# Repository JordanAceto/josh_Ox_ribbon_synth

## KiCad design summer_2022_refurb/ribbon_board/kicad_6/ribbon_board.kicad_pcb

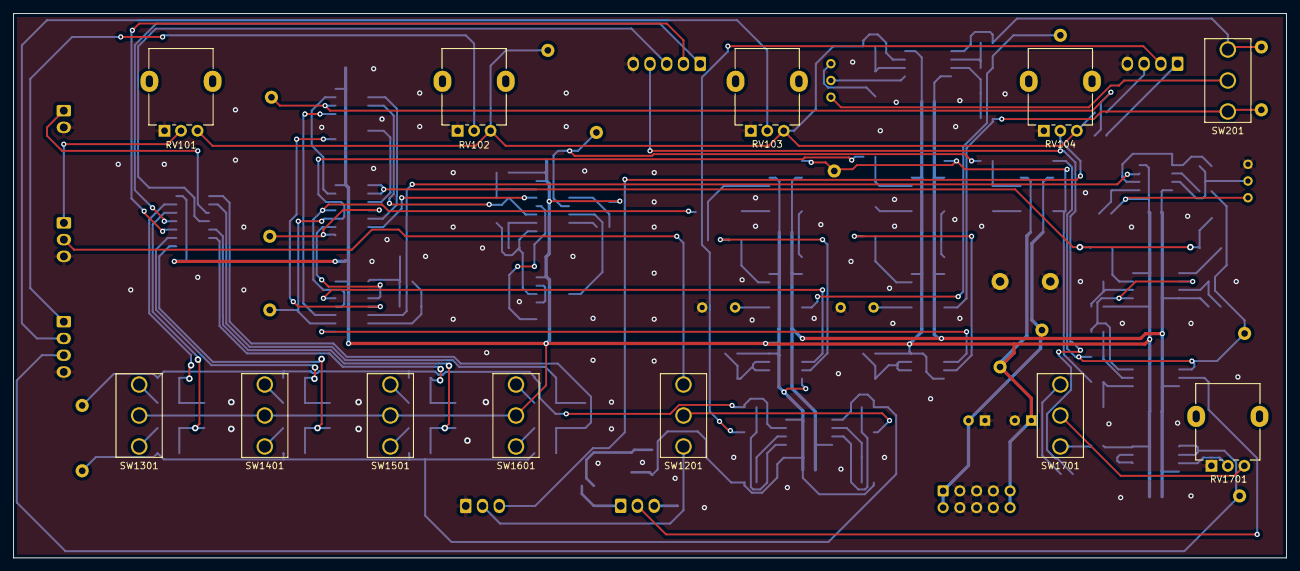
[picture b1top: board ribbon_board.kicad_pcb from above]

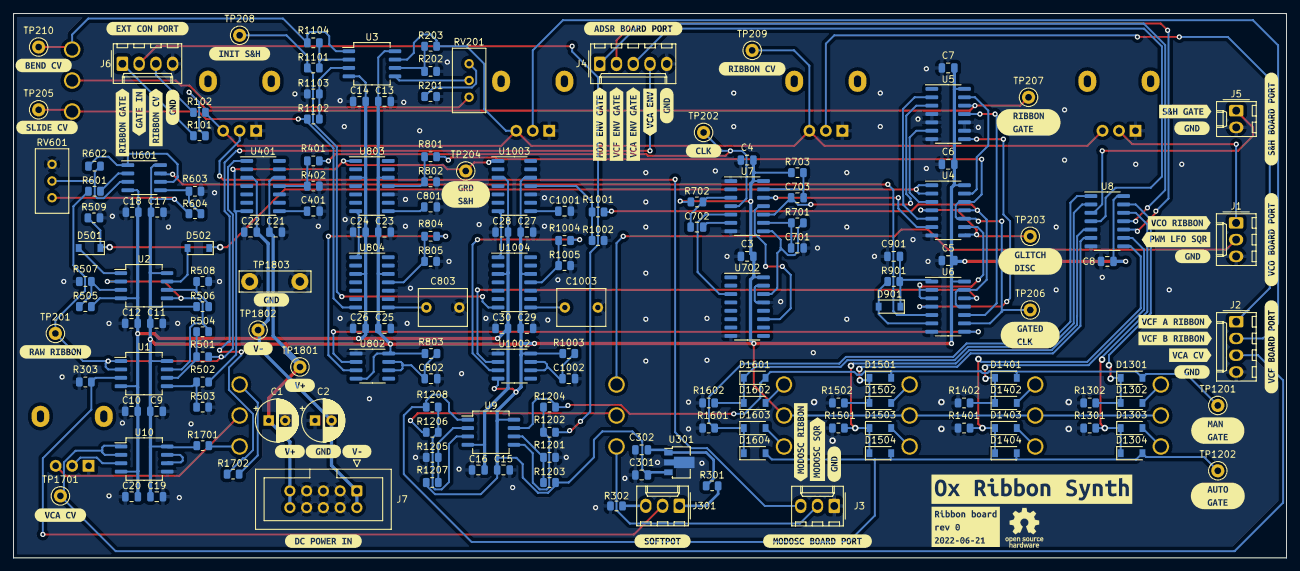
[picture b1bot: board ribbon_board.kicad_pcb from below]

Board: 2 copper layers, 193.0 x 82.5 mm, 229 parts (217 on the bottom side), 115 nets.

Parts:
C1, C2: 10u; CP_Radial_D6.3mm_P2.50mm
C3, C4, C5, C6, C7, C8, C9, C10, C11, C12, C13, C14, C15, C16, C17, C18, C19, C20, C21, C22, C23, C24, C25, C26, C27, C28, C29, C30, C302: 100n; C_0805_2012Metric
C301: 470n; C_0805_2012Metric
C401, C801, C1001: 2n2; C_0805_2012Metric
C701: 1n; C_0805_2012Metric
C702, C703: 4n7; C_0805_2012Metric
C802, C901, C1002: 10n; C_0805_2012Metric
C803, C1003: 1u; C_Rect_L7.2mm_W5.5mm_P5.00mm_FKS2_FKP2_MKS2_MKP2
D501, D502, D901, D1301, D1302, D1303, D1304, D1401, D1402, D1403, D1404, D1501, D1502, D1503, D1504, D1601, D1602, D1603, D1604: 1N4148W; D_SOD-123
J1: VCO_port; Molex_KK-254_AE-6410-03A_1x03_P2.54mm_Vertical
J2: VCF_port; Molex_KK-254_AE-6410-04A_1x04_P2.54mm_Vertical
J3: mod_osc_port; Molex_KK-254_AE-6410-03A_1x03_P2.54mm_Vertical
J4: ADSR_port; Molex_KK-254_AE-6410-05A_1x05_P2.54mm_Vertical
J5: S&H_port; Molex_KK-254_AE-6410-02A_1x02_P2.54mm_Vertical
J6: ext_port; Molex_KK-254_AE-6410-04A_1x04_P2.54mm_Vertical
J7: power_entry; IDC-Header_2x05_P2.54mm_Vertical
J301: ribbon; Molex_KK-254_AE-6410-03A_1x03_P2.54mm_Vertical
R101, R102: 1k; R_0805_2012Metric
R201, R603, R702, R703, R1201, R1202, R1205, R1206: 10k; R_0805_2012Metric
R202, R203, R501, R502, R503, R504, R509, R601, R602, R604, R701, R1101, R1102, R1103, R1104, R1203, R1207, R1301, R1302, R1401, R1402, R1501, R1502, R1601, R1602, R1702: 100k; R_0805_2012Metric
R301: 100; R_0805_2012Metric
R302: 4k7; R_0805_2012Metric
R303, R803, R1003, R1204, R1208: 1M2; R_0805_2012Metric
R401, R801, R804, R1001, R1004: 5k6; R_0805_2012Metric
R402, R802, R805, R1002, R1005: 1k8; R_0805_2012Metric
R505, R506, R1701: 150k; R_0805_2012Metric
R507, R508: 470; R_0805_2012Metric
R901: 120k; R_0805_2012Metric
RV101, RV102, RV103, RV104: 100k c.d.; Potentiometer_Alpha_RD901F-40-00D_Single_Vertical
RV201, RV601: 100k; Potentiometer_Bourns_3296W_Vertical
RV1701: 100k; Potentiometer_Alpha_RD901F-40-00D_Single_Vertical
SW201, SW1201, SW1701: SW_SPDT; SPDT_mini_toggle
SW1301, SW1401, SW1501, SW1601: SW_SPDT_MSM; SPDT_mini_toggle
TP201: raw_ribbon; TestPoint_Keystone_5000-5004_Miniature
TP202: clk; TestPoint_Keystone_5000-5004_Miniature
TP203: glitch_dis; TestPoint_Keystone_5000-5004_Miniature
TP204: guard_s_and_h; TestPoint_Keystone_5000-5004_Miniature
TP205: slide_s_and_h; TestPoint_Keystone_5000-5004_Miniature
TP206: gated_clk; TestPoint_Keystone_5000-5004_Miniature
TP207: gate; TestPoint_Keystone_5000-5004_Miniature
TP208: init_s_and_h; TestPoint_Keystone_5000-5004_Miniature
TP209: ribbon_cv; TestPoint_Keystone_5000-5004_Miniature
TP210: bend_cv; TestPoint_Keystone_5000-5004_Miniature
TP1201: man_gate; TestPoint_Keystone_5000-5004_Miniature
TP1202: audo_gate; TestPoint_Keystone_5000-5004_Miniature
TP1701: vca_cv; TestPoint_Keystone_5000-5004_Miniature
TP1801: V+; TestPoint_Keystone_5000-5004_Miniature
TP1802: V-; TestPoint_Keystone_5000-5004_Miniature
TP1803: GND; TestPoint_Bridge_Pitch7.62mm_Drill1.3mm
U1, U2, U3, U9, U10: TL072; SO-8_5.3x6.2mm_P1.27mm
U4, U8: 4081; SOIC-14_3.9x8.7mm_P1.27mm
U5: 4013; SOIC-14_3.9x8.7mm_P1.27mm
U6, U7: 40106; SOIC-14_3.9x8.7mm_P1.27mm
U301: L78L10_SOT89; SOT-89-3
U401, U803, U804, U1003, U1004: LF398_SOIC14; SOIC-14_3.9x8.7mm_P1.27mm
U601: LM358; SOIC-8_3.9x4.9mm_P1.27mm
U702: 4017; SOIC-16_3.9x9.9mm_P1.27mm
U802, U1002: TLC555xD; SOIC-8_3.9x4.9mm_P1.27mm
kibuzzard-62AC7A9F: G***; kibuzzard-62AC7A9F
kibuzzard-62B1F2D1, kibuzzard-62B1F2D1#2, kibuzzard-62B1F2D1#3, kibuzzard-62B1F2D1#4, kibuzzard-62B1F2D1#5, kibuzzard-62B1F2D1#6, kibuzzard-62B1F2D1#7, kibuzzard-62B1F2D1#8: G***; kibuzzard-62B1F2D1
kibuzzard-62B1F3ED: G***; kibuzzard-62B1F3ED
kibuzzard-62B1F4B1: G***; kibuzzard-62B1F4B1
kibuzzard-62B1F4C1: G***; kibuzzard-62B1F4C1
kibuzzard-62B1F7DB: G***; kibuzzard-62B1F7DB
kibuzzard-62B1F7F1: G***; kibuzzard-62B1F7F1
kibuzzard-62B1F8A8: G***; kibuzzard-62B1F8A8
kibuzzard-62B1F8CB: G***; kibuzzard-62B1F8CB
kibuzzard-62B1F8F4: G***; kibuzzard-62B1F8F4
kibuzzard-62B1F9D0: G***; kibuzzard-62B1F9D0
kibuzzard-62B1F45D: G***; kibuzzard-62B1F45D
kibuzzard-62B1F49A: G***; kibuzzard-62B1F49A
kibuzzard-62B1F53B: G***; kibuzzard-62B1F53B
kibuzzard-62B1F72D: G***; kibuzzard-62B1F72D
kibuzzard-62B1F77F: G***; kibuzzard-62B1F77F
kibuzzard-62B1F525: G***; kibuzzard-62B1F525
kibuzzard-62B1F567: G***; kibuzzard-62B1F567
kibuzzard-62B1F712: G***; kibuzzard-62B1F712
kibuzzard-62B1F743: G***; kibuzzard-62B1F743
kibuzzard-62B1F752: G***; kibuzzard-62B1F752
kibuzzard-62B1F821: G***; kibuzzard-62B1F821
kibuzzard-62B1F904: G***; kibuzzard-62B1F904
kibuzzard-62B1F917: G***; kibuzzard-62B1F917
kibuzzard-62B1F959, kibuzzard-62B1F959#2: G***; kibuzzard-62B1F959
kibuzzard-62B1F963, kibuzzard-62B1F963#2: G***; kibuzzard-62B1F963
kibuzzard-62B1FC16: G***; kibuzzard-62B1FC16
kibuzzard-62B1FC43: G***; kibuzzard-62B1FC43
kibuzzard-62B1FC58: G***; kibuzzard-62B1FC58
kibuzzard-62B1FC81: G***; kibuzzard-62B1FC81
kibuzzard-62B1FCCC: G***; kibuzzard-62B1FCCC
kibuzzard-62B1FD45: G***; kibuzzard-62B1FD45
kibuzzard-62B1FD51: G***; kibuzzard-62B1FD51
kibuzzard-62B1FD62: G***; kibuzzard-62B1FD62
kibuzzard-62B1FDDB: G***; kibuzzard-62B1FDDB
kibuzzard-62B1FE6D: G***; kibuzzard-62B1FE6D
kibuzzard-62B1FEB0: G***; kibuzzard-62B1FEB0
kibuzzard-62B1FECC: G***; kibuzzard-62B1FECC
kibuzzard-62B235EB: G***; kibuzzard-62B235EB
kibuzzard-62B239A3: G***; kibuzzard-62B239A3
kibuzzard-62B23681: G***; kibuzzard-62B23681

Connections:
+15V: C1.1, C3.1, C4.1, C5.1, C6.1, C7.1, C8.1, C9.1, C11.1, C13.1, C15.1, C17.1, C19.1, C21.1, C23.1, C25.1, C27.1, C29.1, C301.1, J7.9, J7.10, R506.1, R604.2, R702.1, R703.1, R803.1, R1003.1, R1203.2, R1207.2, R1701.1, RV601.3, SW1301.2, SW1401.2, SW1501.2, SW1601.2, TP1801.1, U1.8 (V+), U2.8 (V+), U3.8 (V+), U4.14 (VDD), U5.14 (VDD), U6.14 (VDD), U7.14 (VDD), U8.14 (VDD), U9.8 (V+), U10.8 (V+), U301.3 (IN), U401.12 (V+), U601.8 (V+), U702.16 (VDD), U802.4 (R), U802.8 (VCC), U803.12 (V+), U804.12 (V+), U1002.4 (R), U1002.8 (VCC), U1003.12 (V+), U1004.12 (V+)
-15V: C2.2, C10.2, C12.2, C14.2, C16.2, C18.2, C20.2, C22.2, C24.2, C26.2, C28.2, C30.2, J7.1, J7.2, R505.2, TP1802.1, U1.4 (V-), U2.4 (V-), U3.4 (V-), U9.4 (V-), U10.4 (V-), U401.3 (V-), U601.4 (V-), U803.3 (V-), U804.3 (V-), U1003.3 (V-), U1004.3 (V-)
/GATE_IN: J6.2, R1202.1
/MOD_OSC_RIBBON_CTL: J3.3, RV104.2
/MOD_OSC_SQR: J3.2, SW1201.1 (A)
/PWM_LFO_SQR: J1.2, SW1201.3 (C)
/RIBBON_CV: R102.2, R203.2, RV101.3, RV102.3, RV103.3, RV104.3, TP209.1, U3.7
/RIBBON_GATE: R101.2, TP207.1, U5.12 (~Q)
/VCA_ADSR: J4.4, R1702.1
/VCA_CV: J2.3, TP1701.1, U10.1, U10.2 (-)
/VCF_A_RIBBON_CTL: J2.1, RV102.2
/VCF_B_RIBBON_CTL: J2.2, RV103.2
/VCO_RIBBON_CTL: J1.1, RV101.2
/gate_controller/MOD_ENV_GATE: J4.1, U8.11
/gate_controller/S&H_GATE: J5.1, U8.3
/gate_controller/VCA_ADSR_gate_logic/AUTO_GATE: D1304.2 (A), D1404.2 (A), D1504.2 (A), D1604.2 (A), R1208.2, TP1202.1, U9.1
/gate_controller/VCA_ADSR_gate_logic/RIBBON_GATE: D1301.2 (A), D1401.2 (A), D1501.2 (A), D1601.2 (A), R1204.2, TP1201.1, U9.7
/gate_controller/VCA_ENV_GATE: J4.3, U8.4
/gate_controller/VCF_ENV_GATE: J4.2, U8.10
/ribbon_controller/BEND_CV: R1104.2, SW201.3 (C), TP210.1, U3.1
/ribbon_controller/SLIDE_CV: R1102.1, SW201.1 (A), TP205.1, U804.7
/ribbon_controller/TRIG_0: R401.1, TP202.1, U7.4
/ribbon_controller/TRIG_9: U4.6, U7.12
/ribbon_controller/bend_scaler/INIT_IN: R1101.1, TP208.1, U1004.7
/ribbon_controller/comparator/COMP_OUT: U6.5, U601.7
/ribbon_controller/comparator/SIGNAL_IN: R501.1, R601.1, TP201.1, U1.1, U1.2 (-), U401.1 (I)
/ribbon_controller/gate_conditioner/GATED_CLK: R801.1, TP206.1, U4.10, U4.12, U6.9
/ribbon_controller/gate_conditioner/GD_IN: TP203.1, U4.4, U4.8
/ribbon_controller/gate_conditioner/S&H_TRIG: R1001.1, U4.11, U6.11, U6.13
/ribbon_controller/glitch_discriminator/S&H_RIBBON: R502.1, TP204.1, U401.7, U803.1 (I), U1003.1 (I)
/ribbon_controller/~CLK_9: C703.1, U5.3 (C), U7.10
GND: C1.2, C2.1, C3.2, C4.2, C5.2, C6.2, C7.2, C8.2, C9.2, C10.1, C11.2, C12.1, C13.2, C14.1, C15.2, C16.1, C17.2, C18.1, C19.2, C20.1, C21.2, C22.1, C23.2, C24.1, C25.2, C26.1, C27.2, C28.1, C29.2, C30.1, C301.2, C302.2, C401.2, C701.2, C801.2, C802.2, C803.2, C901.2, C1001.2, C1002.2, C1003.2, J1.3, J2.4, J3.1, J4.5, J5.2, J6.4, J7.3, J7.4, J7.5, J7.6, J7.7, J7.8, R201.2, R202.1, R302.2, R303.2, R402.2, R503.2, R507.1, R508.2, R509.2, R603.1, R802.2, R805.2, R1002.2, R1005.2, R1103.1, R1201.1, R1205.1, R1301.2, R1302.2, R1401.2, R1402.2, R1501.2, R1502.2, R1601.2, R1602.2, RV101.1, RV102.1, RV103.1, RV104.1, RV601.1, RV1701.1, TP1803.1, U4.7 (VSS), U5.4 (R), U5.5 (D), U5.7 (VSS), U5.9 (D), U5.10 (R), U6.7 (VSS), U7.1, U7.7 (VSS), U8.7 (VSS), U10.5 (+), U301.2 (GND), U401.10 (T), U702.8 (VSS), U702.13 (CKEN), U702.15 (Reset), U802.1 (GND), U803.10 (T), U804.10 (T), U1002.1 (GND), U1003.10 (T), U1004.10 (T)
unnamed: C302.1, R301.1, U301.1 (OUT)
unnamed: C401.1, U401.8 (Ch)
unnamed: C701.1, R701.1, U7.9
unnamed: C702.1, U7.6
unnamed: C702.2, R702.2, U7.3
unnamed: C703.2, R703.2, U7.13
unnamed: C801.1, U803.8 (Ch)
unnamed: C802.1, R803.2, U802.6 (THR), U802.7 (DIS)
unnamed: C803.1, U804.8 (Ch)
unnamed: C901.1, D901.1 (K), R901.2, U6.1
unnamed: C1001.1, U1003.8 (Ch)
unnamed: C1002.1, R1003.2, U1002.6 (THR), U1002.7 (DIS)
unnamed: C1003.1, U1004.8 (Ch)
unnamed: D501.1 (K), D502.1 (K), R509.1, U4.1, U4.2
unnamed: D501.2 (A), U2.1
unnamed: D502.2 (A), U2.7
unnamed: D901.2 (A), R901.1, U6.6
unnamed: D1301.1 (K), D1302.1 (K), R1302.1, U8.13
unnamed: D1302.2 (A), SW1301.3
unnamed: D1303.1 (K), D1304.1 (K), R1301.1, U8.12
unnamed: D1303.2 (A), SW1301.1
unnamed: D1401.1 (K), D1402.1 (K), R1402.1, U8.9
unnamed: D1402.2 (A), SW1401.3
unnamed: D1403.1 (K), D1404.1 (K), R1401.1, U8.8
unnamed: D1403.2 (A), SW1401.1
unnamed: D1501.1 (K), D1502.1 (K), R1502.1, U8.6
unnamed: D1502.2 (A), SW1501.3
unnamed: D1503.1 (K), D1504.1 (K), R1501.1, U8.5
unnamed: D1503.2 (A), SW1501.1
unnamed: D1601.1 (K), D1602.1 (K), R1602.1, U8.2
unnamed: D1602.2 (A), SW1601.3
unnamed: D1603.1 (K), D1604.1 (K), R1601.1, U8.1
unnamed: D1603.2 (A), SW1601.1
unnamed: J6.1, R101.1
unnamed: J6.3, R102.1
unnamed: J301.1, R301.2
unnamed: J301.2, R303.1, U1.3 (+)
unnamed: J301.3, R302.1
unnamed: R201.1, RV201.1
unnamed: R202.2, R203.1, U3.6 (-)
unnamed: R401.2, R402.1, U401.11 (Hold)
unnamed: R501.2, R504.1, U1.6 (-)
unnamed: R502.2, R503.1, U1.5 (+)
unnamed: R504.2, U1.7, U2.2 (-), U2.5 (+)
unnamed: R505.1, R507.2, U2.3 (+)
unnamed: R506.2, R508.1, U2.6 (-)
unnamed: R601.2, U601.2 (-)
unnamed: R602.1, RV601.2, U601.3 (+)
unnamed: R602.2, U601.1, U601.6 (-)
unnamed: R603.2, R604.1, U601.5 (+)
unnamed: R701.2, U7.8, U702.14 (CLK)
unnamed: R801.2, R802.1, U803.11 (Hold)
unnamed: R804.1, U802.3 (Q)
unnamed: R804.2, R805.1, U804.11 (Hold)
unnamed: R1001.2, R1002.1, U1003.11 (Hold)
unnamed: R1004.1, U1002.3 (Q)
unnamed: R1004.2, R1005.1, U1004.11 (Hold)
unnamed: R1101.2, R1104.1, U3.2 (-)
unnamed: R1102.2, R1103.2, U3.3 (+)
unnamed: R1201.2, R1203.1, U9.6 (-)
unnamed: R1202.2, R1204.1, U9.5 (+)
unnamed: R1205.2, R1207.1, U9.2 (-)
unnamed: R1206.1, SW1201.2 (B)
unnamed: R1206.2, R1208.1, U9.3 (+)
unnamed: R1701.2, SW1701.1 (A)
unnamed: R1702.2, SW1701.3 (C)
unnamed: RV201.2, U3.5 (+)
unnamed: RV201.3, SW201.2 (B)
unnamed: RV1701.2, U10.3 (+)
unnamed: RV1701.3, SW1701.2 (B)
unnamed: U4.3, U5.6 (S)
unnamed: U4.5, U5.2 (~Q)
unnamed: U4.9, U6.2, U6.3
unnamed: U4.13, U5.13 (Q)
unnamed: U5.8 (S), U6.4
unnamed: U5.11 (C), U6.10
unnamed: U6.8, U802.2 (TR)
unnamed: U7.5, U702.3 (Q0)
unnamed: U7.11, U702.11 (Q9)
unnamed: U10.6 (-), U10.7
unnamed: U803.7, U804.1 (I)
unnamed: U6.12, U1002.2 (TR)
unnamed: U1003.7, U1004.1 (I)

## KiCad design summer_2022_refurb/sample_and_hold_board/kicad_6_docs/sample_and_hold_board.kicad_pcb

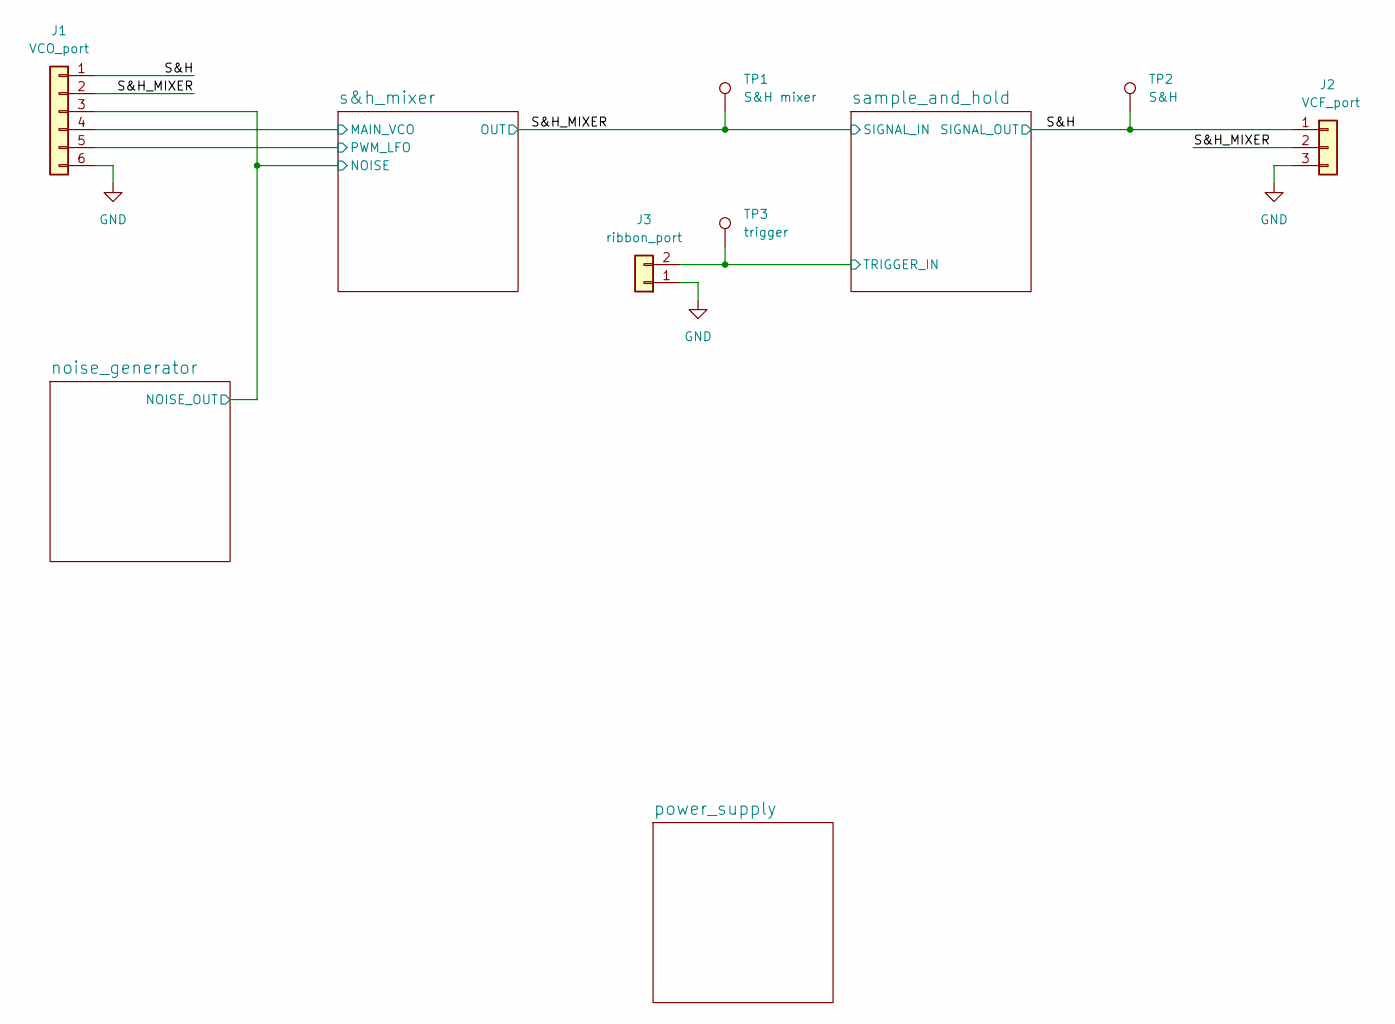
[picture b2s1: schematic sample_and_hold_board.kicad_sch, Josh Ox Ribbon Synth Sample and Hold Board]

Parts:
J1: VCO_port; Molex_KK-254_AE-6410-06A_1x06_P2.54mm_Vertical
J2: VCF_port; Molex_KK-254_AE-6410-03A_1x03_P2.54mm_Vertical
J3: ribbon_port; Molex_KK-254_AE-6410-02A_1x02_P2.54mm_Vertical
TP1: S&H mixer; TestPoint_Keystone_5000-5004_Miniature
TP2: S&H; TestPoint_Keystone_5000-5004_Miniature
TP3: trigger; TestPoint_Keystone_5000-5004_Miniature

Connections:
/S&H: J1.1, J2.1, TP2.1; also elsewhere on the board
/S&H_MIXER: J1.2, J2.2, TP1.1; also elsewhere on the board
/noise_generator/NOISE_OUT: J1.3; also elsewhere on the board
/s&h_mixer/MAIN_VCO: J1.4; also elsewhere on the board
/s&h_mixer/PWM_LFO: J1.5; also elsewhere on the board
/sample_and_hold/TRIGGER_IN: J3.2, TP3.1; also elsewhere on the board
GND: J1.6, J2.3, J3.1; also elsewhere on the board

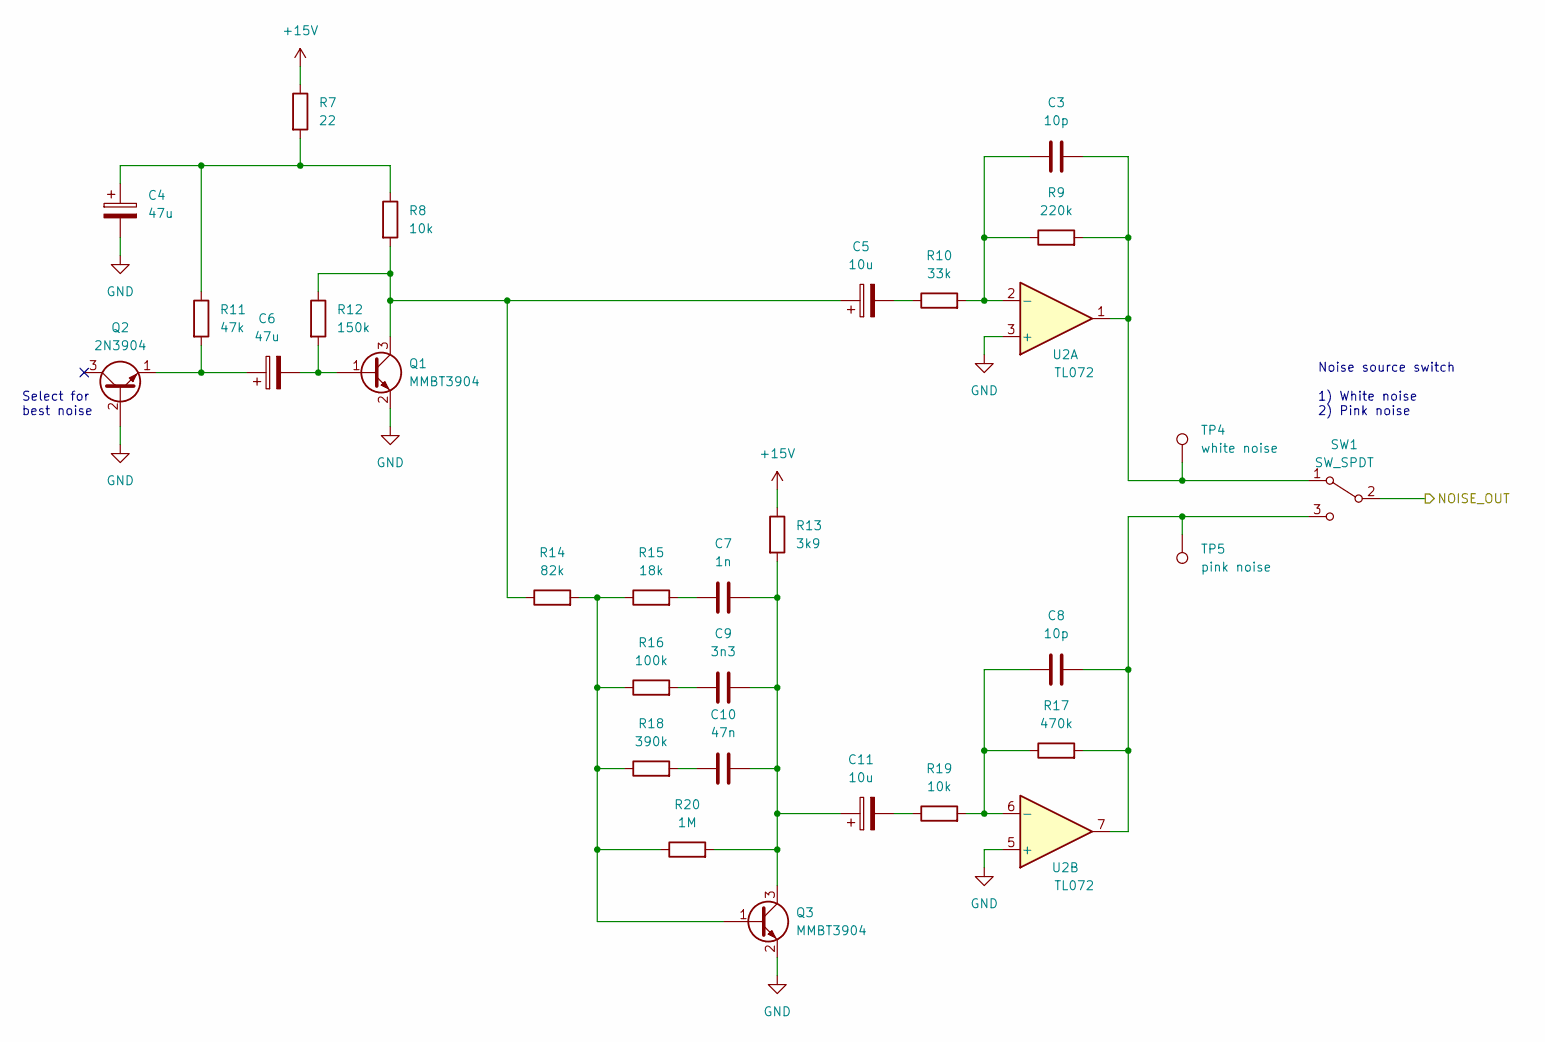
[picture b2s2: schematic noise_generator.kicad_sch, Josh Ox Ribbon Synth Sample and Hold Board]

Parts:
C3, C8: 10p; C_0805_2012Metric
C4, C6: 47u; CP_Radial_D6.3mm_P2.50mm
C5, C11: 10u; CP_Radial_D6.3mm_P2.50mm
C7: 1n; C_0805_2012Metric
C9: 3n3; C_0805_2012Metric
C10: 47n; C_0805_2012Metric
Q1, Q3: MMBT3904; SOT-23
Q2: 2N3904; TO-92_Inline_Wide
R7: 22; R_0805_2012Metric
R8, R19: 10k; R_0805_2012Metric
R9: 220k; R_0805_2012Metric
R10: 33k; R_0805_2012Metric
R11: 47k; R_0805_2012Metric
R12: 150k; R_0805_2012Metric
R13: 3k9; R_0805_2012Metric
R14: 82k; R_0805_2012Metric
R15: 18k; R_0805_2012Metric
R16: 100k; R_0805_2012Metric
R17: 470k; R_0805_2012Metric
R18: 390k; R_0805_2012Metric
R20: 1M; R_0805_2012Metric
SW1: SW_SPDT; SPDT_mini_toggle
TP4: white noise; TestPoint_Keystone_5000-5004_Miniature
TP5: pink noise; TestPoint_Keystone_5000-5004_Miniature
U2: TL072; SO-8_5.3x6.2mm_P1.27mm

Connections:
+15V: R7.1, R13.1; also elsewhere on the board
/noise_generator/NOISE_OUT: SW1.2 (B); also elsewhere on the board
GND: C4.2, Q1.2 (E), Q2.2 (B), Q3.2 (E), U2.3 (+), U2.5 (+); also elsewhere on the board
unnamed: C3.1, R9.1, R10.2, U2.2 (-)
unnamed: C3.2, R9.2, SW1.1 (A), TP4.1, U2.1
unnamed: C4.1, R7.2, R8.1, R11.1
unnamed: C5.1, Q1.3 (C), R8.2, R12.1, R14.1
unnamed: C5.2, R10.1
unnamed: C6.1, Q2.1 (E), R11.2
unnamed: C6.2, Q1.1 (B), R12.2
unnamed: C7.1, R15.2
unnamed: C8.1, R17.1, R19.2, U2.6 (-)
unnamed: C8.2, R17.2, SW1.3 (C), TP5.1, U2.7
unnamed: C9.1, R16.2
unnamed: C10.1, R18.2
unnamed: C7.2, C9.2, C10.2, C11.1, Q3.3 (C), R13.2, R20.2
unnamed: C11.2, R19.1
unnamed: Q3.1 (B), R14.2, R15.1, R16.1, R18.1, R20.1

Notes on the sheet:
Noise source switch 1) White noise 2) Pink noise
Select for best noise

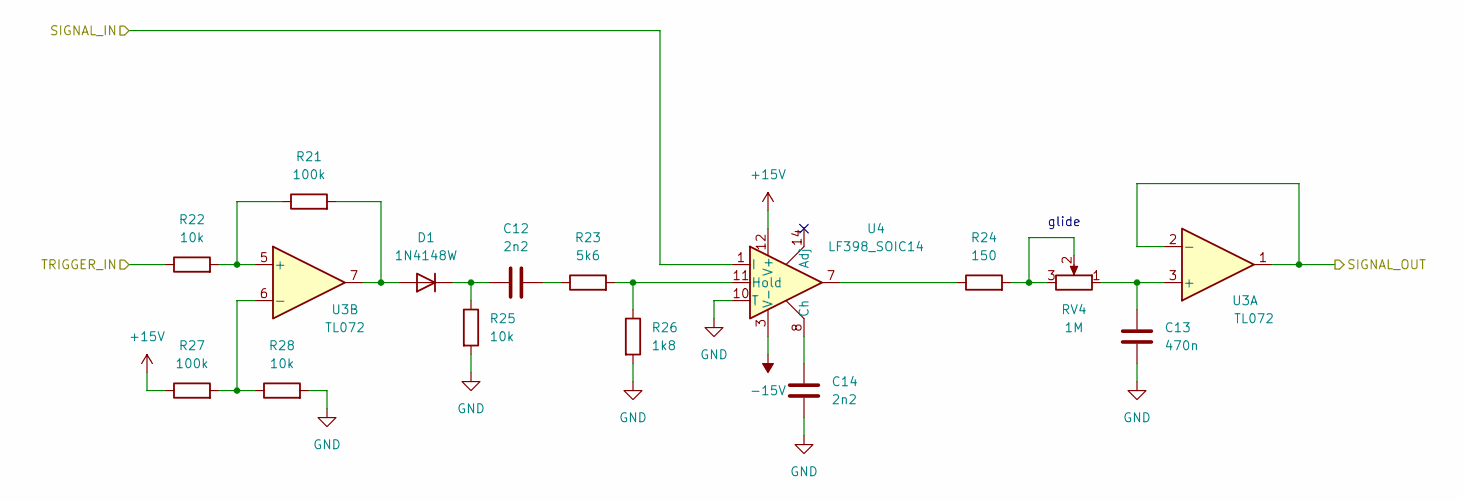
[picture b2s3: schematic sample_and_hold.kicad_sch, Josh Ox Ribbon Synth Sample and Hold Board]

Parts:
C12: 2n2; C_0805_2012Metric
C13: 470n; C_Rect_L7.2mm_W5.5mm_P5.00mm_FKS2_FKP2_MKS2_MKP2
C14: 2n2; C_Rect_L7.2mm_W2.5mm_P5.00mm_FKS2_FKP2_MKS2_MKP2
D1: 1N4148W; D_SOD-123
R21, R27: 100k; R_0805_2012Metric
R22, R25, R28: 10k; R_0805_2012Metric
R23: 5k6; R_0805_2012Metric
R24: 150; R_0805_2012Metric
R26: 1k8; R_0805_2012Metric
RV4: 1M; Potentiometer_Alpha_RD901F-40-00D_Single_Vertical
U3: TL072; SO-8_5.3x6.2mm_P1.27mm
U4: LF398_SOIC14; SOIC-14_3.9x8.7mm_P1.27mm

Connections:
+15V: R27.1, U4.12 (V+); also elsewhere on the board
-15V: U4.3 (V-); also elsewhere on the board
/S&H: U3.1, U3.2 (-); also elsewhere on the board
/S&H_MIXER: U4.1 (I); also elsewhere on the board
/sample_and_hold/TRIGGER_IN: R22.1; also elsewhere on the board
GND: C13.2, C14.2, R25.2, R26.2, R28.2, U4.10 (T); also elsewhere on the board
unnamed: C12.1, D1.1 (K), R25.1
unnamed: C12.2, R23.1
unnamed: C13.1, RV4.1, U3.3 (+)
unnamed: C14.1, U4.8 (Ch)
unnamed: D1.2 (A), R21.2, U3.7
unnamed: R21.1, R22.2, U3.5 (+)
unnamed: R23.2, R26.1, U4.11 (Hold)
unnamed: R24.1, U4.7
unnamed: R24.2, RV4.2, RV4.3
unnamed: R27.2, R28.1, U3.6 (-)

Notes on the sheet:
glide

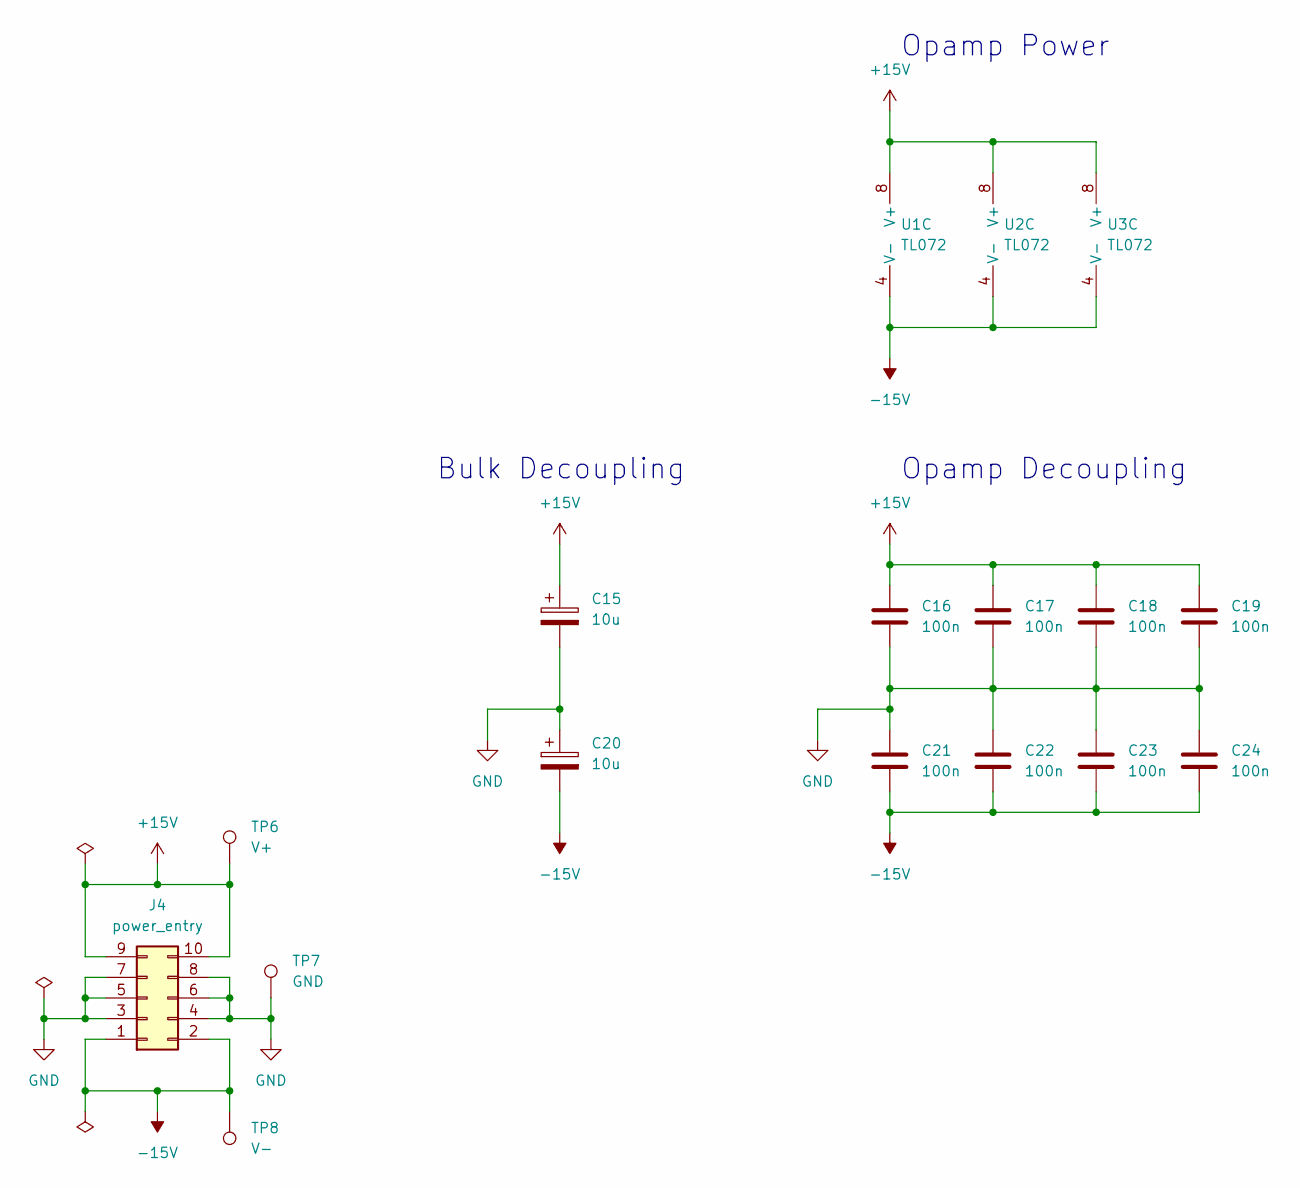
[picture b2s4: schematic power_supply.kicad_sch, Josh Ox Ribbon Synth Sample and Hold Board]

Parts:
C15, C20: 10u; CP_Radial_D6.3mm_P2.50mm
C16, C17, C18, C19, C21, C22, C23, C24: 100n; C_0805_2012Metric
J4: power_entry; IDC-Header_2x05_P2.54mm_Vertical
TP6: V+; TestPoint_Keystone_5000-5004_Miniature
TP7: GND; TestPoint_Bridge_Pitch7.62mm_Drill1.3mm
TP8: V-; TestPoint_Keystone_5000-5004_Miniature
U1, U2, U3: TL072; SO-8_5.3x6.2mm_P1.27mm

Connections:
+15V: C15.1, C16.1, C17.1, C18.1, C19.1, J4.9, J4.10, TP6.1, U1.8 (V+), U2.8 (V+), U3.8 (V+); also elsewhere on the board
-15V: C20.2, C21.2, C22.2, C23.2, C24.2, J4.1, J4.2, TP8.1, U1.4 (V-), U2.4 (V-), U3.4 (V-); also elsewhere on the board
GND: C15.2, C16.2, C17.2, C18.2, C19.2, C20.1, C21.1, C22.1, C23.1, C24.1, J4.3, J4.4, J4.5, J4.6, J4.7, J4.8, TP7.1; also elsewhere on the board

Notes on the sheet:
Opamp Decoupling
Opamp Power
Bulk Decoupling

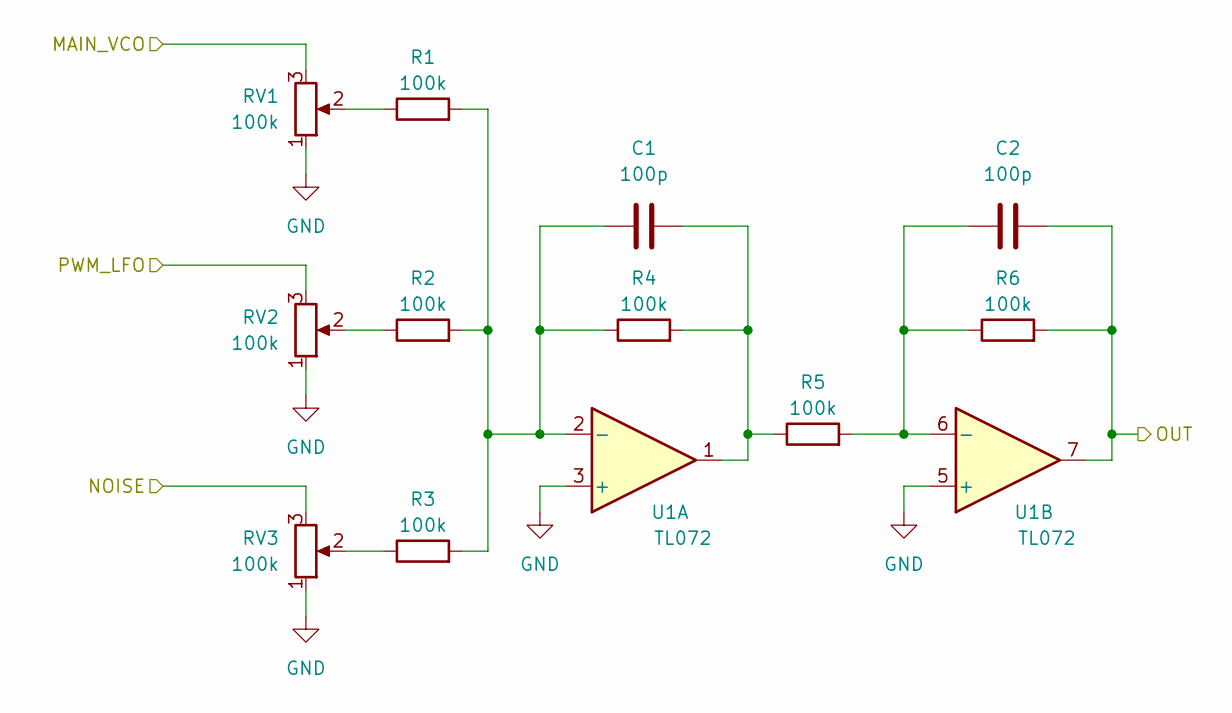
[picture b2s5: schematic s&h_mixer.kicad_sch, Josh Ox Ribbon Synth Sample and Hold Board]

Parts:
C1, C2: 100p; C_0805_2012Metric
R1, R2, R3, R4, R5, R6: 100k; R_0805_2012Metric
RV1, RV2, RV3: 100k; Potentiometer_Alpha_RD901F-40-00D_Single_Vertical
U1: TL072; SO-8_5.3x6.2mm_P1.27mm

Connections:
/S&H_MIXER: C2.2, R6.2, U1.7; also elsewhere on the board
/noise_generator/NOISE_OUT: RV3.3; also elsewhere on the board
/s&h_mixer/MAIN_VCO: RV1.3; also elsewhere on the board
/s&h_mixer/PWM_LFO: RV2.3; also elsewhere on the board
GND: RV1.1, RV2.1, RV3.1, U1.3 (+), U1.5 (+); also elsewhere on the board
unnamed: C1.1, R1.2, R2.2, R3.2, R4.1, U1.2 (-)
unnamed: C1.2, R4.2, R5.1, U1.1
unnamed: C2.1, R5.2, R6.1, U1.6 (-)
unnamed: R1.1, RV1.2
unnamed: R2.1, RV2.2
unnamed: R3.1, RV3.2

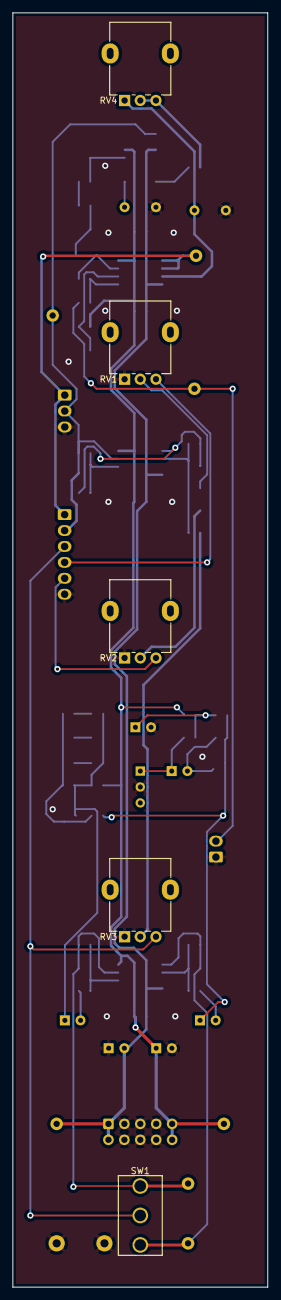
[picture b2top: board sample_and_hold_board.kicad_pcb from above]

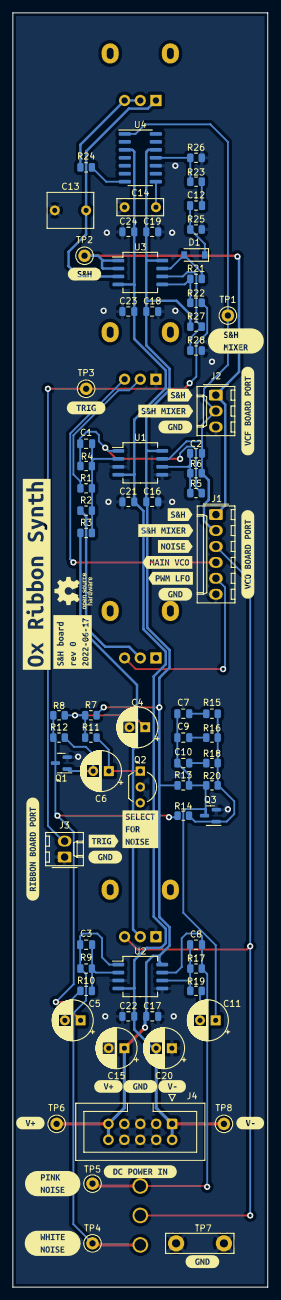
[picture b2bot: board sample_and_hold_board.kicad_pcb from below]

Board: 2 copper layers, 40.6 x 203.2 mm, 106 parts (101 on the bottom side), 40 nets.

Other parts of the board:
kibuzzard-62AC7A9F: G***; kibuzzard-62AC7A9F
kibuzzard-62AC78CB: G***; kibuzzard-62AC78CB
kibuzzard-62AC81C6: G***; kibuzzard-62AC81C6
kibuzzard-62AC81E3: G***; kibuzzard-62AC81E3
kibuzzard-62AC82BB: G***; kibuzzard-62AC82BB
kibuzzard-62AC82DF: G***; kibuzzard-62AC82DF
kibuzzard-62AC755C, kibuzzard-62AC755C#2, kibuzzard-62AC755C#3, kibuzzard-62AC755C#4, kibuzzard-62AC755C#5: G***; kibuzzard-62AC755C
kibuzzard-62AC791A, kibuzzard-62AC791A#2: G***; kibuzzard-62AC791A
kibuzzard-62AC792A, kibuzzard-62AC792A#2: G***; kibuzzard-62AC792A
kibuzzard-62AC813F, kibuzzard-62AC813F#2: G***; kibuzzard-62AC813F
kibuzzard-62AC818C: G***; kibuzzard-62AC818C
kibuzzard-62AC819F: G***; kibuzzard-62AC819F
kibuzzard-62AC822A: G***; kibuzzard-62AC822A
kibuzzard-62AC8121: G***; kibuzzard-62AC8121
kibuzzard-62AC8151, kibuzzard-62AC8151#2: G***; kibuzzard-62AC8151
kibuzzard-62AC8170: G***; kibuzzard-62AC8170
kibuzzard-62AC8211: G***; kibuzzard-62AC8211
kibuzzard-62AC8240: G***; kibuzzard-62AC8240
kibuzzard-62AC8254: G***; kibuzzard-62AC8254
kibuzzard-62AC8271: G***; kibuzzard-62AC8271
kibuzzard-62AC8282: G***; kibuzzard-62AC8282

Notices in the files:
summer_2022_refurb/VCF_VCA_board/power_supply.kicad_sch:
creativecommons.org/licenses/by/4.0
License: CC by 4.0
summer_2022_refurb/ribbon_board/kicad_6/power_supply.kicad_sch:
creativecommons.org/licences/by/4.0
